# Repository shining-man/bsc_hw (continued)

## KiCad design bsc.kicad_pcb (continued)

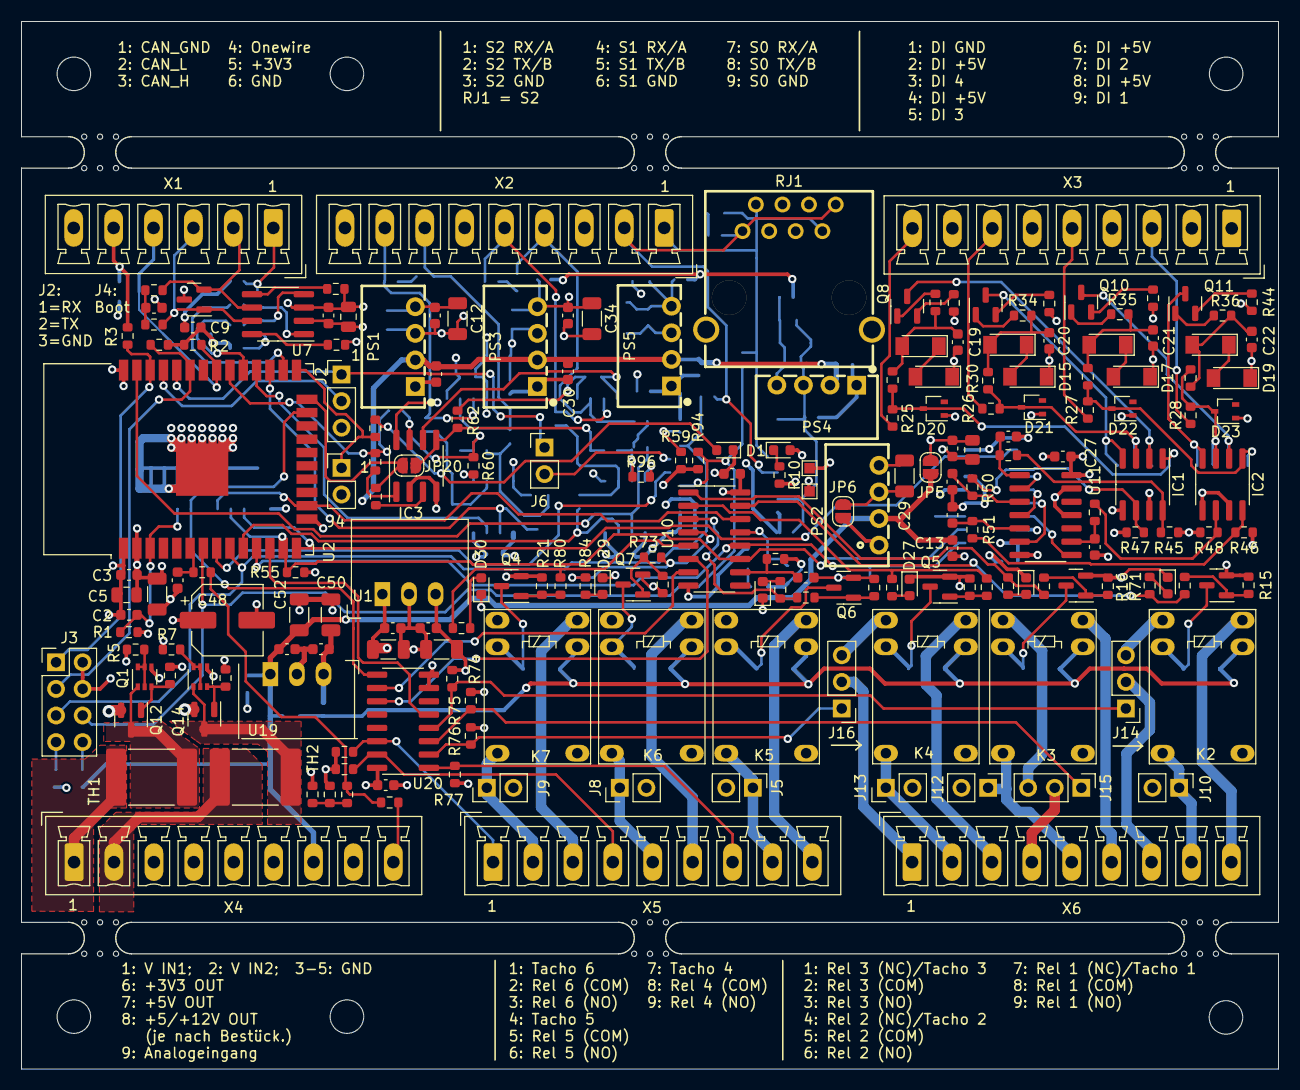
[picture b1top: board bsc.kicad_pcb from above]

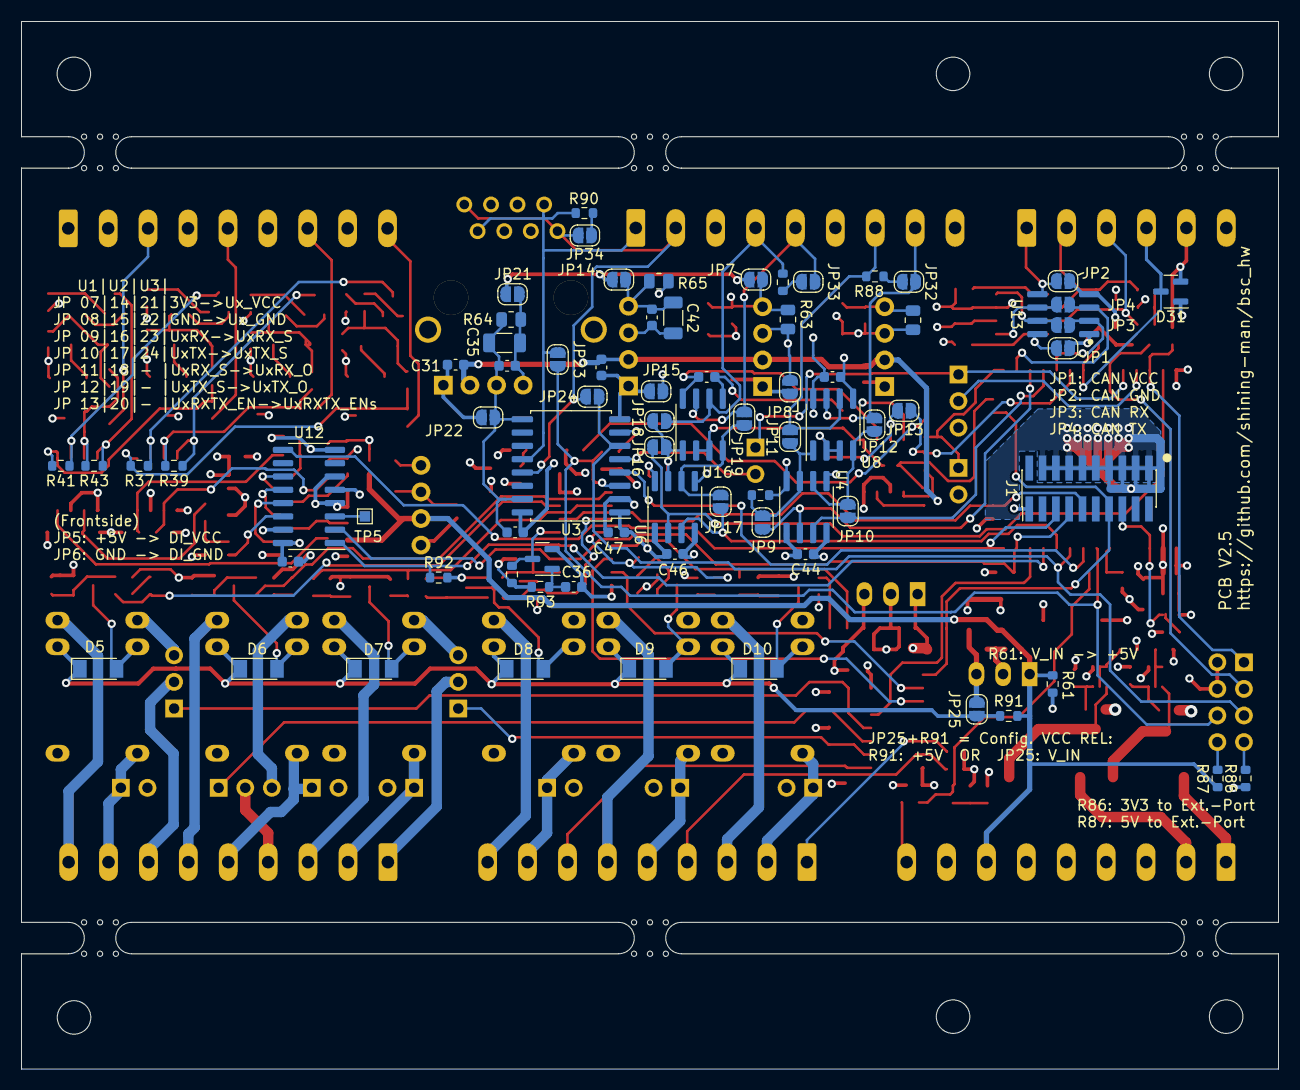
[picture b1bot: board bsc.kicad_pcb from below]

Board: 4 copper layers, 120.0 x 100.0 mm, 286 parts (75 on the bottom side), 175 nets.

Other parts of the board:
C36: 10uF; C_0603_1608Metric
mouse-bite-3mm-slot, mouse-bite-3mm-slot#2, mouse-bite-3mm-slot#3, mouse-bite-3mm-slot#4, mouse-bite-3mm-slot#5, mouse-bite-3mm-slot#6: VAL**; mouse-bite-3mm-slot

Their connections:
GND: C36.2; also elsewhere on the board

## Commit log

2022-10-20 Initial version
2022-11-29 Redesign PCB
2022-12-17 Layout optimized
2023-04-01 Change extension bus
2023-04-01 change picture
2023-07-21 Ref 2.4
2023-11-23 Improvements added (Ref 2.4.1)
2023-11-23 Track spacing in layout corrected
2023-12-16 Slikscreen changed
2024-03-25 Fix pullup
2024-03-29 RX Pullups von U1+U2 geändert
2024-04-07 Version geändert
2024-04-17 Layoutänderungen
